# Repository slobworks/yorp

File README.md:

**New!** Version 0.2 adds a full amp of extra current capacity, and has adjustable output. 3.6V output now stably handles CPUs that require just a wee bit more voltage than 3.3V on the nose, and the extra current ought to improve operation with Cyrix 5x86 CPUs.

If anyone really wants to replace an LT1085 doing 3.3V duty on a 486 motherboard with a buck converter equivalent and doesn't mind the prospect of rewiring some stuff for it, I've made 'Yorp', a three pin buck converter board based on the Diodes AP63301WU 3A Synchronous Buck. 

I've made one of these and put it in my PB450 motherboard based Packard Bell Legend 10CDT, where it works quite well driving an Am5x86 at 133MHz.

Depending on how the LT1085 is set up on your motherboard, you _might_ have to remove some parts and do some rewiring so that the GND terminal actually goes to GND without causing something else on the motherboard to misbehave. As always, rigorously check for bad things like short circuits to ground using a multimeter before applying power!

Bill of materials:

-1x AP63301WU Adjustable Buck Regulator in SOT-23-5 (https://www.digikey.com/en/products/detail/diodes-incorporated/AP63301WU-7/10491607)

-1x 107K 0805/2012 metric SMD resistor

-1x 30.1K 0805/2012 metric SMD resistor

-5x 10uF 25V 2012/3216 metric SMD ceramic caps, X5R/X7R 

-1x 100nF 0805/2012 metric SMD ceramic cap, C0G

-1x 51pF 0805/2012 metric SMD ceramic cap, C0G

-1x 4.7uH 6.3mm x 6.3mm SMD inductor rated for _at least_ 4.5A saturation current (I used one of these: https://www.digikey.com/en/products/detail/murata-electronics/1255AY-4R7M-P3/5271453)

-1x 2.54mm pitch, 3-pin, pin header

Some Q&A:

**Why would I want to do this?**
- Reduce heat generated by the 3.3V regulation (Yorp runs just barely above room temperature when powering an Am5x86 at 133MHz, compared to the LT1085 quickly reaching first degree burn-inflicting temperature)
- Improve electrical efficiency of your 486 system
- Coolness factor (be the first kid on your block with an 80 plus capable vintage computer, after putting a modern PSU with an ATX->AT adaptor on your machine!)

**Would this work with an Intel 486DX4 or Am5x86-133?**

Yep!

**Would this work with a Cyrix 5x86-100/120?**

Starting with Version 0.2, Yorp should provide sufficient voltage and current capacity to hopefully run the Cyrix 5x86-type CPUs stably.

**Wait a minute! The far left pin is the ADJUST pin for the LT1085! How the hell am I going to get GROUND there?**

That is up to you to figure out. While not a particularly difficult mod to build, the implementation will require you to study your 486 motherboard a bit first before jumping in. On my Packard Bell PB450 motherboard, all I had to do was remove any resistors on R124 and R131, and short R131 together using a little snipped piece of capacitor leg. Your board will certainly vary, so study it up first!

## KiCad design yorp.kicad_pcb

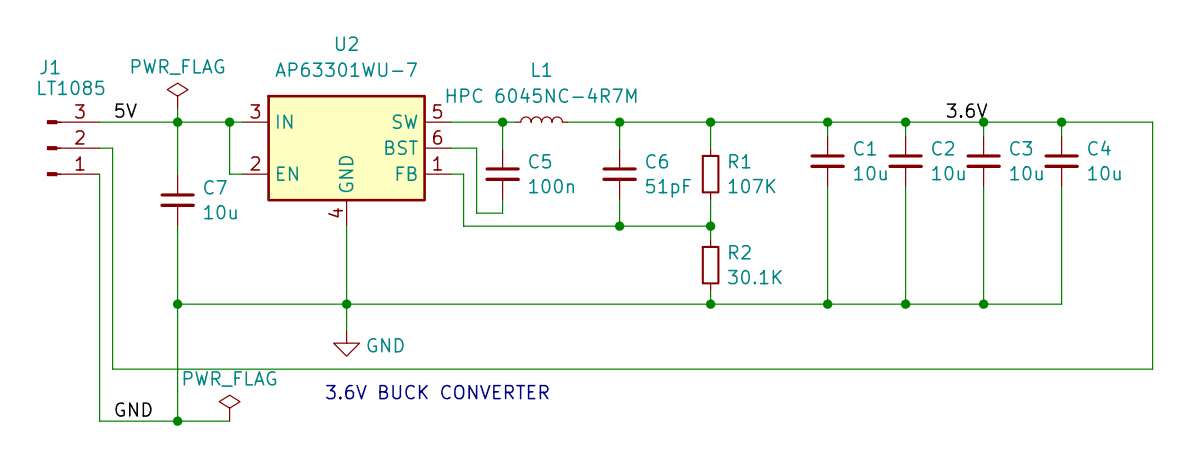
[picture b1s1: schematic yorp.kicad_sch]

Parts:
C1, C2, C3, C4, C7: 10u; C_1206_3216Metric
C5: 100n; C_0805_2012Metric
C6: 51pF; C_0805_2012Metric
J1: LT1085; PinHeader_1x03_P2.54mm_Vertical
L1: HPC 6045NC-4R7M; L_6.3x6.3_H3
R1: 107K; R_0805_2012Metric
R2: 30.1K; R_0805_2012Metric
U2: AP63301WU-7; TSOT-23-6

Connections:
/3.6V: C1.1, C2.1, C3.1, C4.1, C6.1, J1.2, L1.2, R1.1
/5V: C7.1, J1.3, U2.2 (EN), U2.3 (IN)
GND: C1.2, C2.2, C3.2, C4.2, C7.2, J1.1, R2.2, U2.4 (GND)
unnamed: C5.2, U2.6 (BST)
unnamed: C6.2, R1.2, R2.1, U2.1 (FB)
unnamed: C5.1, L1.1, U2.5 (SW)

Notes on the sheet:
3.6V BUCK CONVERTER

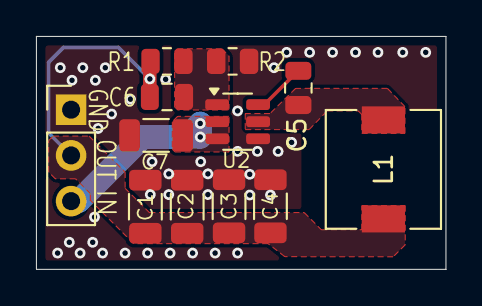
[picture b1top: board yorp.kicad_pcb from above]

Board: 4 copper layers, 22.8 x 12.9 mm, 12 parts (0 on the bottom side), 6 nets.

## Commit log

2025-07-05 Add files via upload
    Updated to 0.2
2026-01-19 Add files via upload
    Updated component values.
